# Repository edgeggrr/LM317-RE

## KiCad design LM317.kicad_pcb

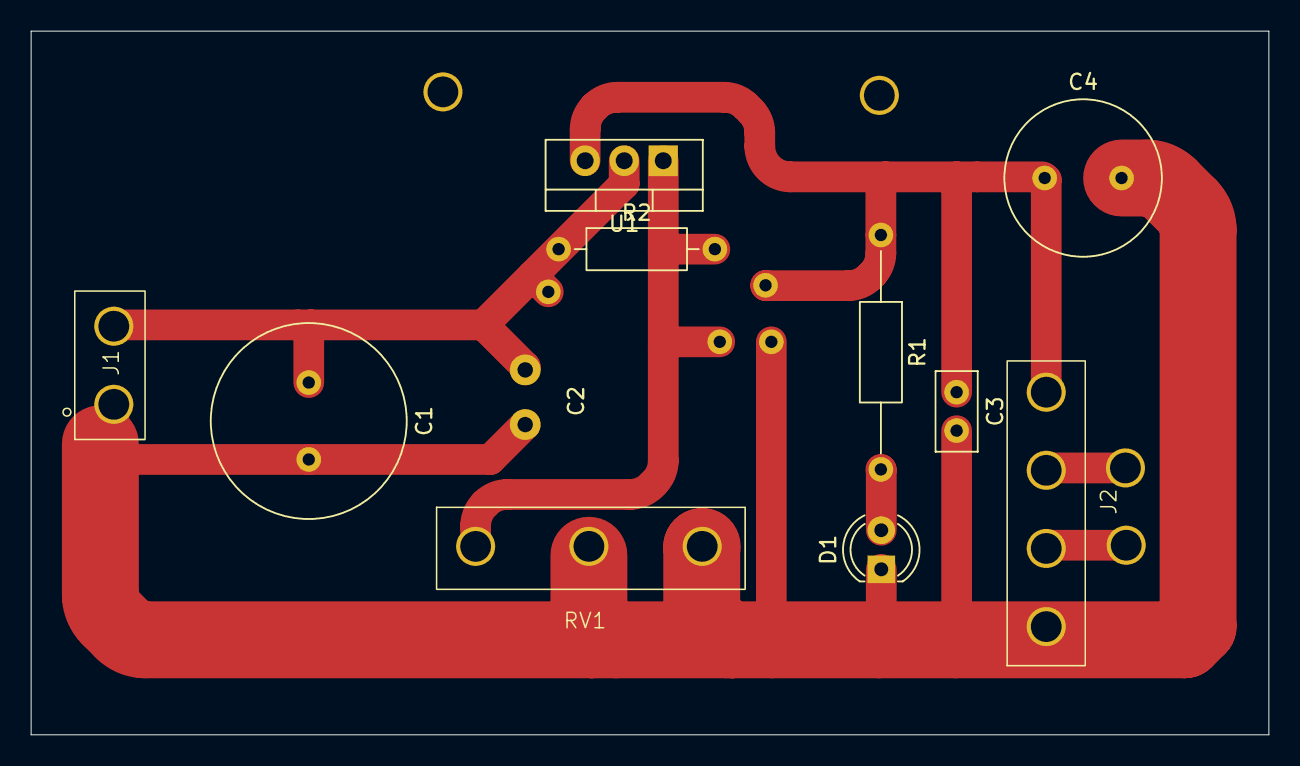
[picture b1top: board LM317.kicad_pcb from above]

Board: 2 copper layers, 80.5 x 45.8 mm, 11 parts (0 on the bottom side), 5 nets.

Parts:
C1: C; C_Radial_D12.5mm_H25.0mm_P5.00mm
C2: C; C_Disc_D11.0mm_W5.0mm_P5.00mm
C3: C; C_Disc_D5.0mm_W2.5mm_P2.50mm
C4: C; C_Radial_D10.0mm_H12.5mm_P5.00mm
D1: LED; LED_D4.0mm
J1: Output Terminal; Screw Terminal-2
J2: Input Terminal; Screw Terminal
R1: R_US; R_Axial_DIN0207_L6.3mm_D2.5mm_P15.24mm_Horizontal
R2: R_US; R_Axial_DIN0207_L6.3mm_D2.5mm_P10.16mm_Horizontal
RV1: 4.7k; POT
U1: LM317_TO-220; TO-220-3_Vertical

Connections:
GND: C1.2, C2.2, C3.2, C4.2, D1.1 (K), J1.1, J2.2, RV1.2, RV1.3
unnamed: D1.2 (A), R1.2
unnamed: C1.1, C2.1, J1.2, R2.1, U1.2 (VO)
unnamed: C3.1, C4.1, J2.1, R1.1, U1.3 (VI)
unnamed: R2.2, RV1.1, U1.1 (ADJ)
